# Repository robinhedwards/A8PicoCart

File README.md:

# A8PicoCart (UnoCart on a Raspberry Pi Pico clone)

The A8PicoCart is a multi-cart for the Atari 8-bit (XL/XE) which you can make at home with only basic soldering skills.
It is based on my earlier UnoCart design but uses a very inexpensive Raspberry Pi Pico clone (£2-3) for an easy build.

When plugged into a PC by USB it becomes a Mass Storage device allowing ROM/CAR/XEX & ATR files to be copied to the cartridge.
When plugged into an Atari these files are shown on the menu and the device will either emulate the selected cartridge type or
act as a XEX file launcher. It also has (very) limited support for ATR files allowing you to do some programming and save your
work to an ATR file.

This page contains everything you need to build the project - firmware to flash to your purple Pico clone, Kicad PCB design files to make a PCB and 3d print files for a nice case. The source code for everything is also here. There is also a manual detailing the full capabilities of the cartridge.

If you build an A8PicoCart consider donating to help fund this and my future projects:

## Quick Start

Get yourself a purple Raspberry Pi Pico clone (see [this thread](https://forums.raspberrypi.com/viewtopic.php?t=337976) for details) and order a PCB using the KiCad board files provided. You have a choice of two PCB designs - the XE design is for use uncased, with the Pico on the top surface. The XL/XE version is desgined to be mounted in a case (though can be used uncased too) with the Pico on the bottom/back surface. Once you have the Pico clone and PCB, solder the pico as pictured below, depending on your PCB version. Program the firmware onto the device by pressing BOOTSEL on the board and connecting to USB on a PC and drag the firmware (UF2 file) onto the device. It should then remount as A8-PICOCART so you can copy Atari CAR & XEX files to it. Unmount, then plug into your Atari and play! Optionally solder a reset button to reset back to the menu.

**Warning**: always disconnect from PC/USB before plugging into your Atari or you will damage your Atari and/or PC. This warning mainly
applies to the XE/uncased version of the PCB. The newest version of the XL/XE board makes it physically impossible to connect USB when the
cartridge is inserted in an Atari.

## Inserting the cartridge

Depending on which PCB you choose the Pico clone may be mounted on the front or back of the PCB. When you insert
the cartridge in the Atari make sure the "S..A" side of the cartridge edge (NOT the "1..15" side) is facing upwards (XE) or towards you (XL).

## Purple Pico clones

The firmware is designed for the Purple Pico clones with USB C connector and 16Megs of flash and a single button (BOOTSEL).
I've received these devices with two different types of SPI flash chips - Winbond and (slower) Z-bit. The firmware has been tested with both types.

The project defines a custom board with a higher value for PICO_FLASH_SPI_CLKDIV so it supports the slower Z-bit flash.

Be aware that it's possible you might get one with another type of flash memory chip that has not been tested.

## Reset button

You can solder a push button to the cartridge to get back to the menu and avoid wear on your Atari power switch.
When you reset the cartridge the Atari will crash - just push reset on the Atari itself to get back to the menu.

The button used is a 6x6mm thru-hole tactile momentary switch. If you are going to print a case, then 9mm+ height is suitable.
When you solder the button to the PCB - make sure the lower two holes in the PCB are bridged only when the button is pressed.

It works simply by pulling the RUN pin on the pico clone to ground to reset.

## 3D print files

The STL files can be used to print a 3 part (front, back and logo) cartridge shell. The 2-tone logo is achieved by
changing the filament at the correct z-position when printing a8pico_logo.stl. You'll also need two M3 15mm screws.

## Changelog

* 7 Oct 2023 - Add new PCB & case design files to make it impossible to insert USB when plugged into Atari. Add support for Microcart (CAR type 52) cartridges. Updated manual.
* 29 Oct 2023 - Adds 3 new cartridge types (thanks to ascrnet)

## Credits

* Design, hardware and firmware by Robin Edwards (electrotrains at atariage)
* XEX loader and OS modifications by Jonathan Halliday (flashjazzcat at atariage)
* Altirra LLE OS used with permision from Avery Lee (phaeron at atariage)

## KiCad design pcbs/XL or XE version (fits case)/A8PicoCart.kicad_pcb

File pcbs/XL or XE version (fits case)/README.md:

## XL/XE version PCB (which fits the 3d printed case design)

* KiCad Project
* A zip file of the gerbers (Elecrow specification).
* Updated version for pico pointing downwards towards cartridge slot

PCB specifications:
1.6mm thickness
Hard gold fingers with bevelled edge will make your PCB last longer, but at a much higher cost.

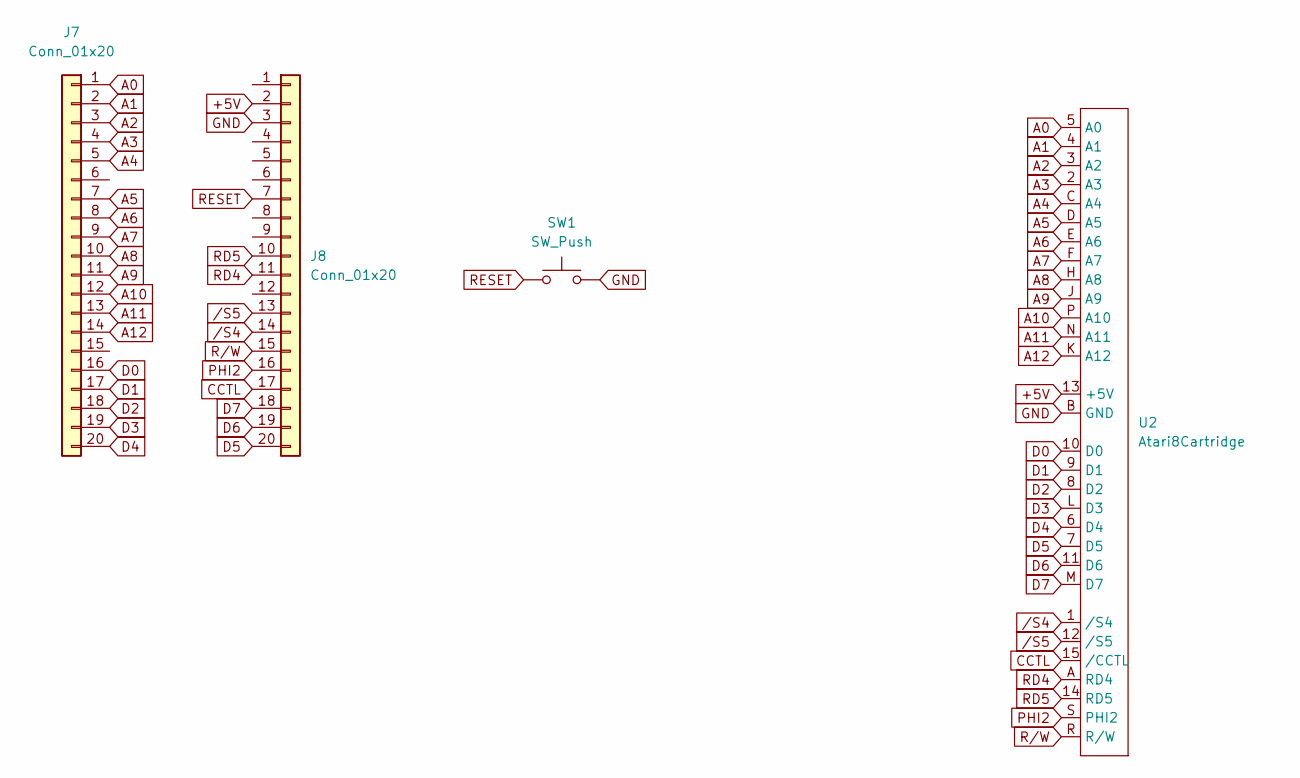
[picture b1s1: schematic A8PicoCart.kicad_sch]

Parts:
J7, J8: Conn_01x20; PinSocket_1x20_P2.54mm_Vertical
SW1: SW_Push; SW_PUSH_6mm_H8mm
U2: Atari8Cartridge; Atari8Cartridge MountHoles

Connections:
+5V: J8.2, U2.13 (+5V)
A0: J7.1, U2.5 (A0)
A1: J7.2, U2.4 (A1)
A2: J7.3, U2.3 (A2)
A3: J7.4, U2.2 (A3)
A4: J7.5, U2.C (A4)
A5: J7.7, U2.D (A5)
A6: J7.8, U2.E (A6)
A7: J7.9, U2.F (A7)
A8: J7.10, U2.H (A8)
A9: J7.11, U2.J (A9)
A10: J7.12, U2.P (A10)
A11: J7.13, U2.N (A11)
A12: J7.14, U2.K (A12)
CCTL: J8.17, U2.15 (/CCTL)
D0: J7.16, U2.10 (D0)
D1: J7.17, U2.9 (D1)
D2: J7.18, U2.8 (D2)
D3: J7.19, U2.L (D3)
D4: J7.20, U2.6 (D4)
D5: J8.20, U2.7 (D5)
D6: J8.19, U2.11 (D6)
D7: J8.18, U2.M (D7)
GND: J8.3, SW1.2, U2.B (GND)
PHI2: J8.16, U2.S (PHI2)
RD4: J8.11, U2.A (RD4)
RD5: J8.10, U2.14 (RD5)
RESET: J8.7, SW1.1
R/W: J8.15, U2.R (R/W)
/S4: J8.14, U2.1 (/S4)
/S5: J8.13, U2.12 (/S5)

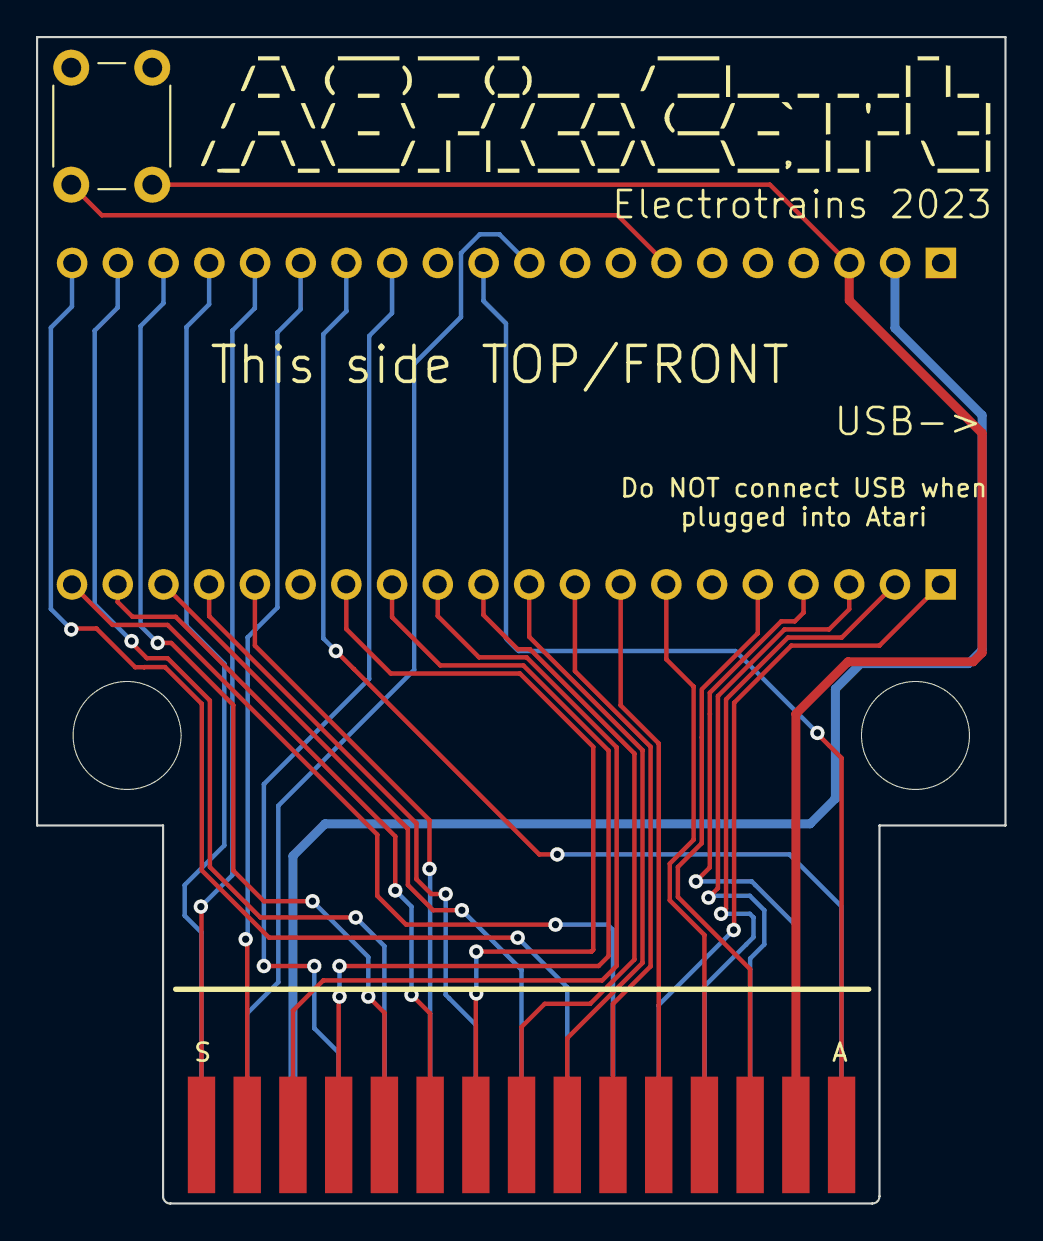
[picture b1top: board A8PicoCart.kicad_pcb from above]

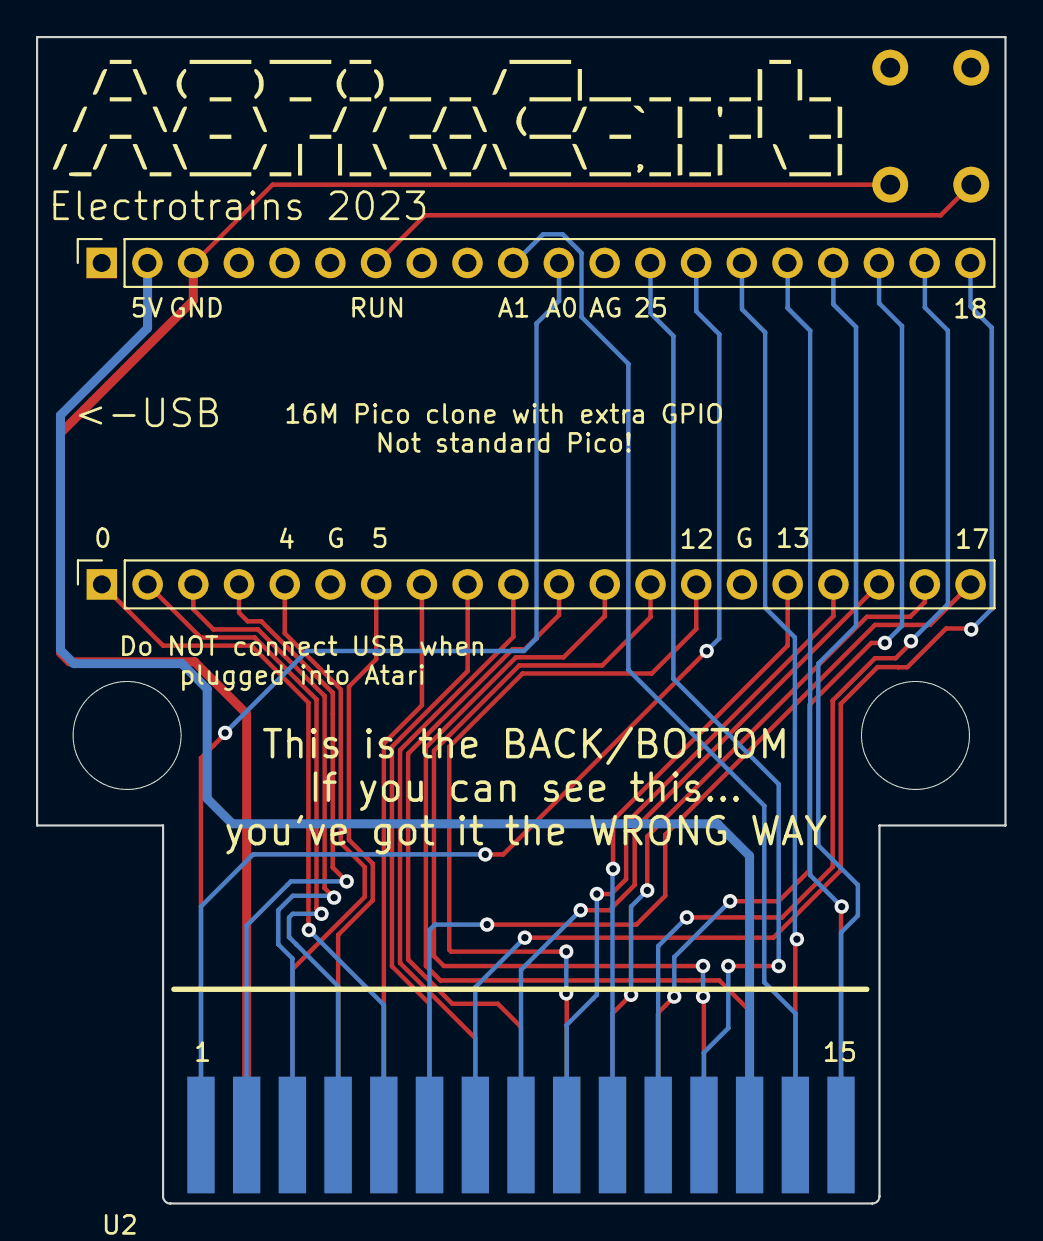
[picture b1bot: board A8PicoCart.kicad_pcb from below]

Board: 2 copper layers, 53.8 x 64.8 mm, 4 parts (3 on the bottom side), 31 nets.

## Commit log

2023-08-02 initial commit of all source files
2023-08-03 reorganise files
2023-08-26 write up
2023-08-26 Update README.md
    more images
2023-08-26 Update README.md
    formatting
2023-08-26 Update README.md
    typo
2023-08-26 tweaks
2023-08-27 add screw specs
2023-08-27 add gerbers
2023-10-07 add microcart cartridge support
2023-10-07 update pcb, case
    remove risk of back powering atari from USB by making it physically impossible on the XL/XE/cased board
2023-10-22 new cartrigdes
    * - Adds Standard 2k cars (CAR type 57)
    * - Adds Phoenix 8k cars (CAR type 39)
    * - Adds Blizzard 4k cars (CAR type 46)
2023-10-29 update firmware after pull request
2023-12-07 support for aDawliah 32K
2023-12-08 support for Turbo 2000 8K
2023-12-18 - put dimension in a common file, add makefile
2023-12-18 - use modules in scad, round corners
2023-12-18 - add clean target to makefile
2023-12-18 - make the corner radius 2mm, reset label, add missing file
2023-12-18 -add recreated STLs
2024-01-25 support for JNSoft 16k
2024-01-31 support for Telelink II 8k
2024-02-06 search and read A8PICOCART.ROM
2024-03-04 Update README.md
    add PCB thickness
2025-02-21 Add include hardware/clocks.h. This fixes building with the latest SDK.
